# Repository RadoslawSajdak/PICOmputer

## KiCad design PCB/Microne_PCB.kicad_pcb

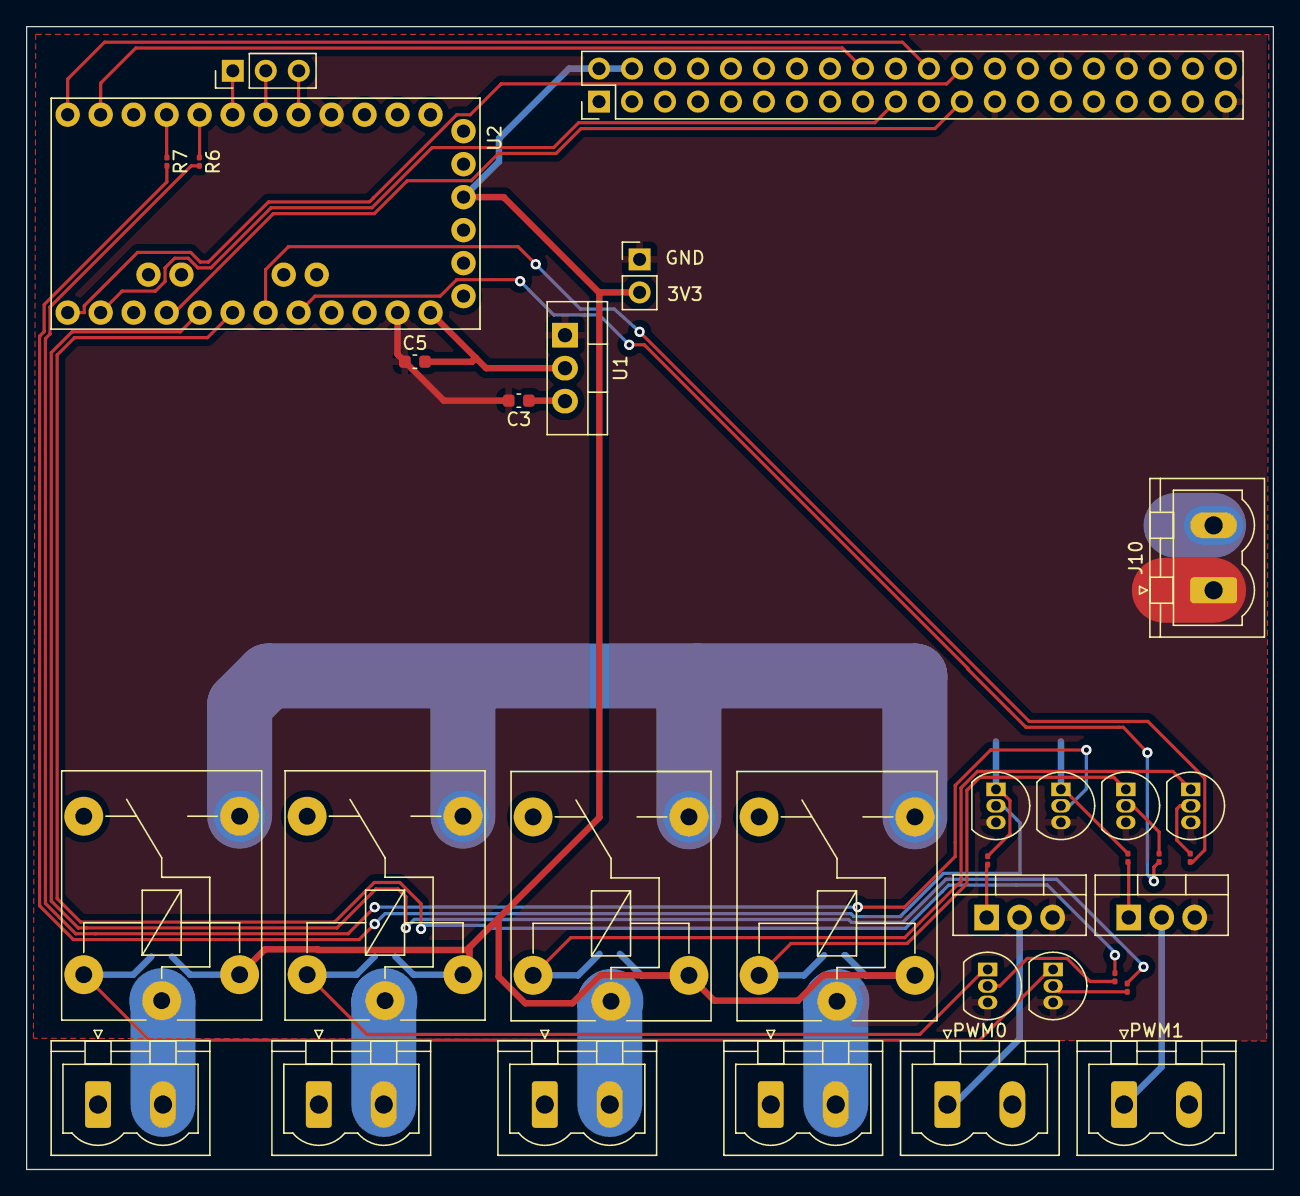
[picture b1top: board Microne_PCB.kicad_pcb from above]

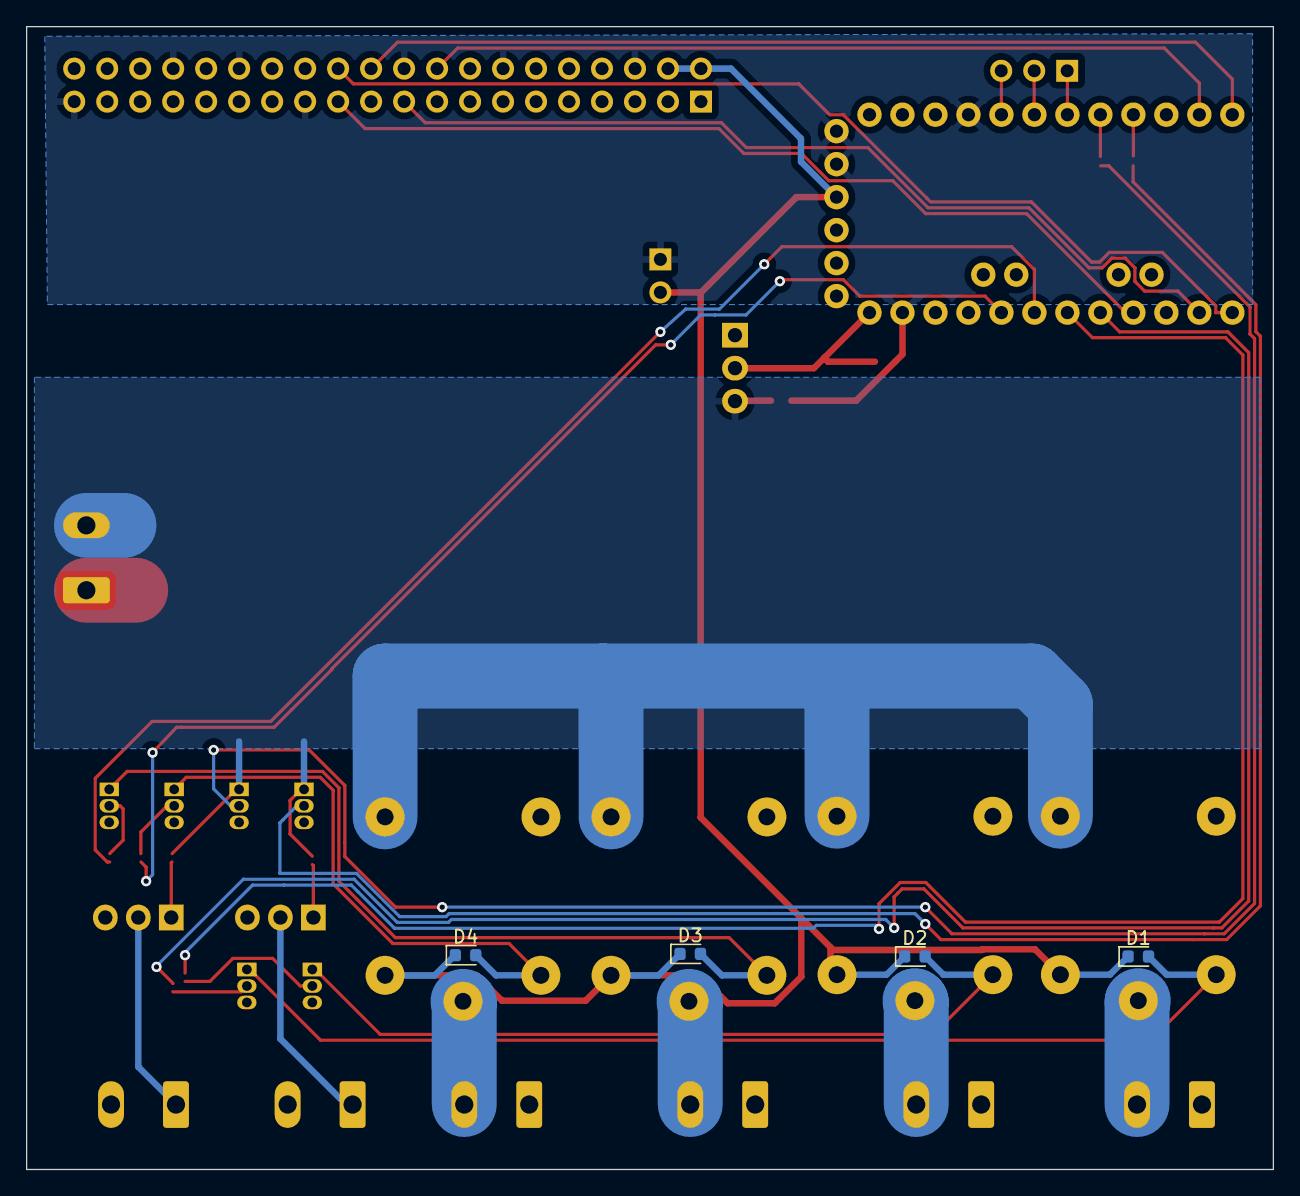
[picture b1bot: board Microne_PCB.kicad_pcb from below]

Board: 2 copper layers, 96.0 x 88.0 mm, 38 parts (4 on the bottom side), 36 nets.

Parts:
C3, C5: 10u; C_0603_1608Metric
D1, D2, D3, D4: D; D_0603_1608Metric
J1: Conn_02x20_Odd_Even; PinHeader_2x20_P2.54mm_Vertical
J2, J3, J4, J5, J6, J7, J10: Conn_01x02_Male; PhoenixContact_MSTBVA_2,5_2-G_1x02_P5.00mm_Vertical
J8: Conn_01x03_Male; PinHeader_1x03_P2.54mm_Vertical
J9: Conn_01x02_Male; PinHeader_1x02_P2.54mm_Vertical
K1, K2, K3, K4: FINDER-36.11; Relay_SPDT_Finder_36.11
Q1, Q2, Q5, Q6, Q7, Q8: BC547; TO-92_Inline
Q3, Q4: IRLZ44N; TO-220-3_Vertical
R6, R7, R8, R9: 10k; R_0201_0603Metric
R10, R11, R12, R13: 1k; R_0201_0603Metric
U1: LM1085-12; TO-220-3_Vertical
U2: ARDUINO_PRO_MINI; MODULE_ARDUINO_PRO_MINI

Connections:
+3.3V: D1.1 (K), D2.1 (K), D3.1 (K), D4.1 (K), J1.2, J1.4, J9.2, K1.A1, K2.A1, K3.A1, K4.A1, U2.JP1_4 (VCC)
+12V: C5.2, U1.2 (VO), U2.JP6_1 (RAW)
/CLK: J1.23, U2.JP6_9 (SCK)
/CS: J1.24, U2.JP6_12 (D10)
/DC: J1.18, U2.JP7_2 (D8)
/DIN: J1.19, U2.JP6_11 (MOSI)
/ENC_A: J8.2, U2.JP7_7 (D3)
/ENC_B: J8.1, U2.JP7_6 (D4)
/ENC_SW: J8.3, U2.JP7_8 (D2)
/PWM_0: R6.1, U2.JP7_5 (D5)
/PWM_1: R7.1, U2.JP7_4 (D6)
/RELAY_0: R10.1, U2.JP6_8 (A0)
/RELAY_1: R11.1, U2.JP6_7 (A1)
/RELAY_2: R12.1, U2.JP6_6 (A2)
/RELAY_3: R13.1, U2.JP6_5 (A3)
/RST: J1.22, U2.JP7_1 (D9)
/Relays1/RELAY_12V_OUT: J3.2, K2.11
/Relays2/RELAY_12V_OUT: J4.2, K3.11
/Relays3/RELAY_12V_OUT: J5.2, K4.11
/Relays/RELAY_12V_OUT: J2.2, K1.11
GND: C3.2, C5.1, J1.6, J1.14, J1.20, J1.25, J1.30, J1.34, J1.39, J9.1, J10.1, Q1.3 (E), Q2.3 (E), Q3.3 (S), Q4.3 (S), Q5.3 (E), Q6.3 (E), Q7.3 (E), Q8.3 (E), U1.1 (GND), U2.JP1_5 (GND), U2.JP1_6 (GND), U2.JP6_2 (GND_1), U2.JP7_9 (GND_2)
unnamed: D1.2 (A), K1.A2, Q5.1 (C)
unnamed: D2.2 (A), K2.A2, Q6.1 (C)
unnamed: D3.2 (A), K3.A2, Q7.1 (C)
unnamed: D4.2 (A), K4.A2, Q8.1 (C)
unnamed: J6.1, Q3.2 (D)
unnamed: J7.1, Q4.2 (D)
unnamed: Q1.2 (B), R6.2
unnamed: Q2.2 (B), R7.2
unnamed: Q3.1 (G), R8.2
unnamed: Q4.1 (G), R9.2
unnamed: Q5.2 (B), R10.2
unnamed: Q6.2 (B), R11.2
unnamed: Q7.2 (B), R12.2
unnamed: Q8.2 (B), R13.2
VDC: C3.1, J10.2, K1.14, K2.14, K3.14, K4.14, Q1.1 (C), Q2.1 (C), R8.1, R9.1, U1.3 (VI)

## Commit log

2022-10-25 Blink
2022-10-25 Encoder prototype
2022-10-26 Removed pico
2022-10-30 Blinkduino
2022-10-30 Encoder
2022-10-30 Working oled prototype
2022-10-30 clearing the code; overflow bugfix
2022-10-31 Wrong schematics
2022-11-01 PCB Prototype
2022-11-24 Working PWM with IRFN
